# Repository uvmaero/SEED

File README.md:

# SEED
23-24 Battery design BMS

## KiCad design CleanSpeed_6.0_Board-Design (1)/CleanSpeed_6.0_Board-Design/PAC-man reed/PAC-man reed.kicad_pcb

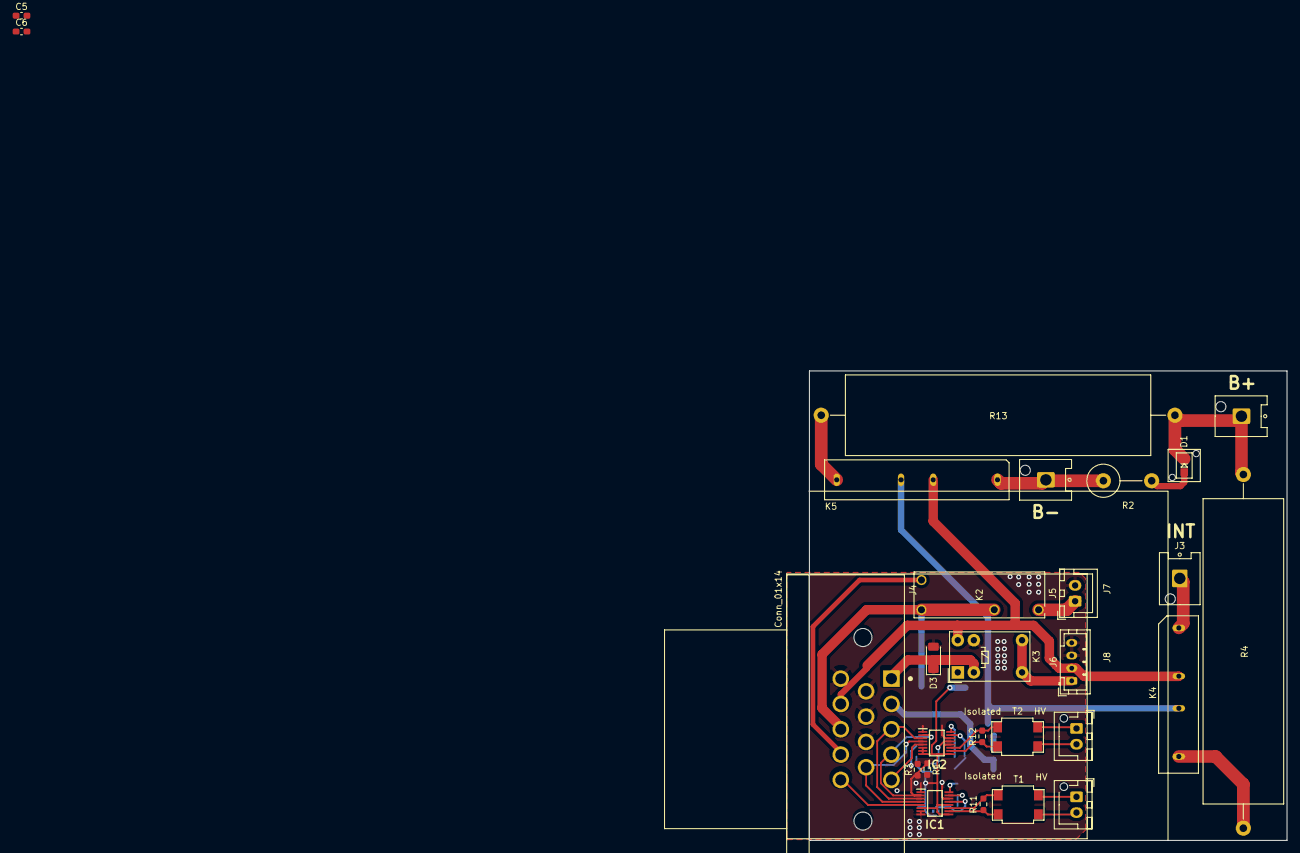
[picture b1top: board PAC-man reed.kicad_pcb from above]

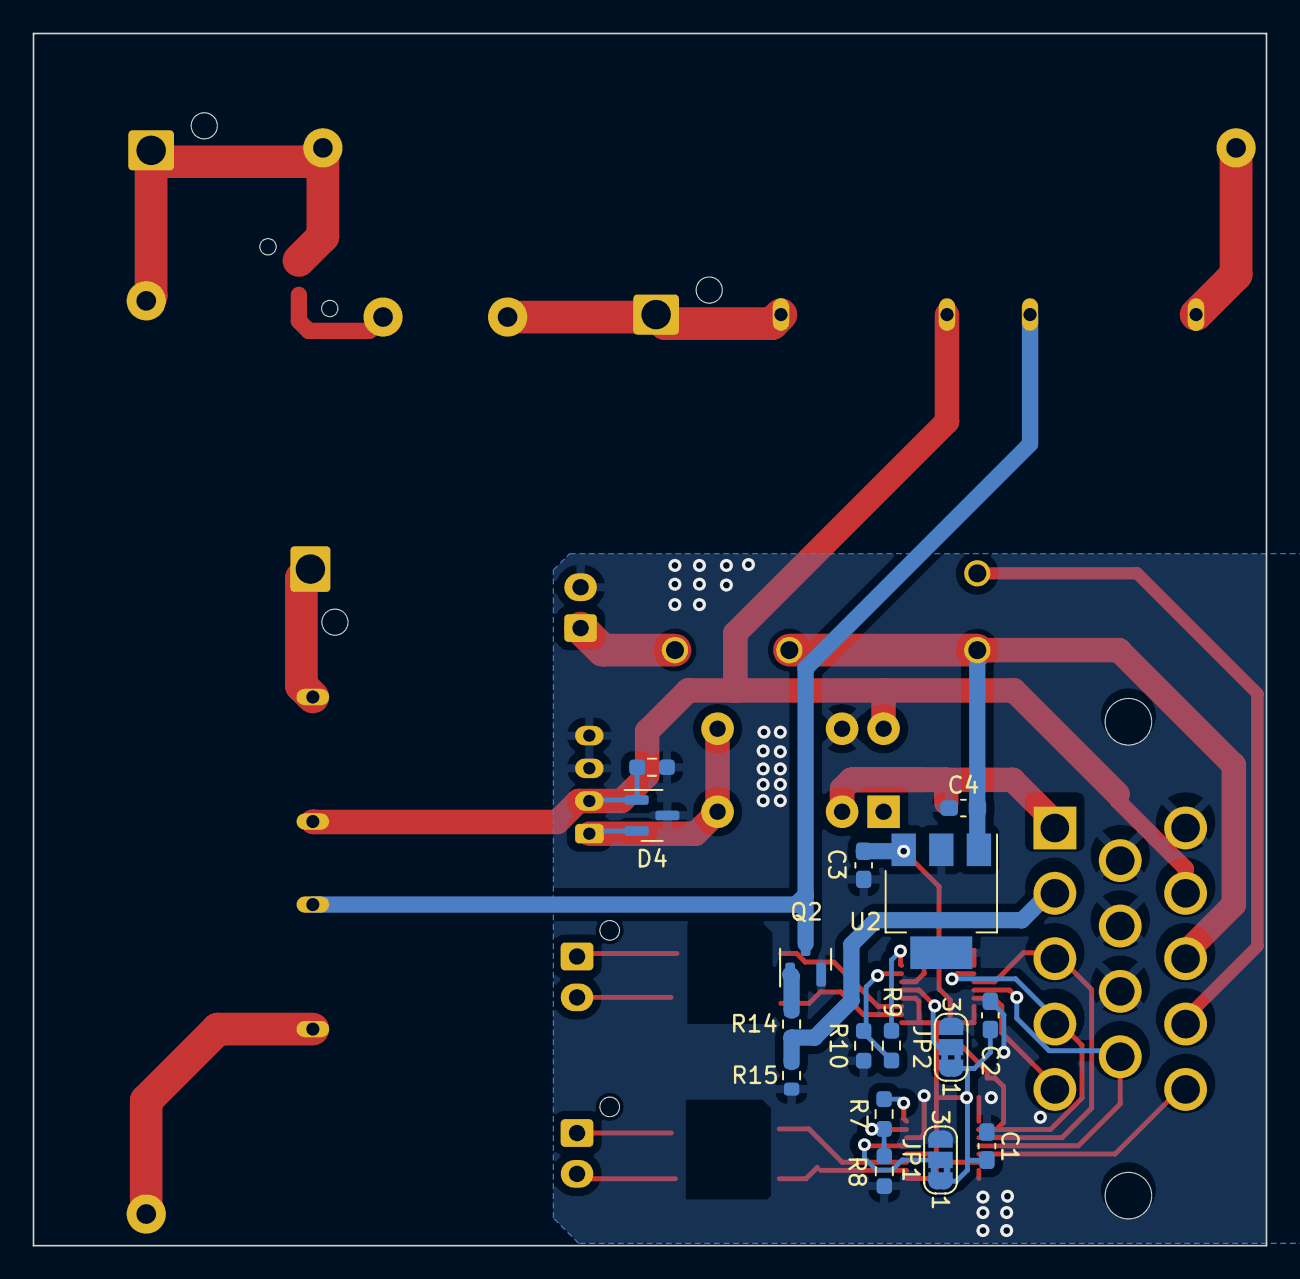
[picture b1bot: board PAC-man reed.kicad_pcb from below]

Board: 2 copper layers, 75.5 x 74.2 mm, 43 parts (16 on the bottom side), 34 nets.

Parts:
C1, C2, C5, C6: .1u; C_0603_1608Metric_Pad1.08x0.95mm_HandSolder
C3, C4: 10u; C_0603_1608Metric_Pad1.08x0.95mm_HandSolder
D1: LED; LPA-C011301S-x LED 0805 LIGHT PIPE SINGLE VERT SMD
D3: 1N4148; D_MiniMELF
D4: MMBZxx; SOT-23
IC1, IC2: LTC6820HMS#3ZZPBF; SOP50P490X110-16N
J1, J2, J3: Conn_01x01; Hirose_DF63M-1P-3.96DSA_1x01_P3.96mm_Vertical
J4: Conn_01x14; TE_1-776266-1_14pin_Horizontal
J5: Conn_01x02; JST_XH_B2B-XH-A_1x02_P2.50mm_Vertical
J6: JST PH; JST_PH_B4B-PH-K_1x04_P2.00mm_Vertical
J7, J8: Conn_01x02; JST_XH_B2B-XH-AM_1x02_P2.50mm_Vertical
JP1, JP2: Fast / Slow; SolderJumper-3_P1.3mm_Bridged2Bar12_RoundedPad1.0x1.5mm_Num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
K2: G5NB-1A4-E DC12; RELAY_G5NB-1A DC5_OMR
K3: G5V-1; Relay_SPDT_Omron_G5V-1
K4: 374-1408-5-ND; SHV12
K5: S1-12-BDM; S1-12
Q2: MMBT2222A; SOT-23
R1, R3: 2k; R_0603_1608Metric_Pad0.98x0.95mm_HandSolder
R2: 1.5k; R_Axial_DIN0516_L15.5mm_D5.0mm_P7.62mm_Vertical
R4: 2.5K; R_Axial_Power_L48.0mm_W12.5mm_P55.88mm
R5: 15k; R_0603_1608Metric_Pad0.98x0.95mm_HandSolder
R7, R8, R9, R10: 1k; R_0603_1608Metric_Pad0.98x0.95mm_HandSolder
R11, R12: 100; R_0603_1608Metric_Pad0.98x0.95mm_HandSolder
R13: 2.5k; R_Axial_Power_L48.0mm_W12.5mm_P55.88mm
R14: 10k; R_0603_1608Metric
R15: 2k; R_0603_1608Metric
T1, T2: ESMIT-4180_C; SOIC4_CBM4D19_SUM
U2: LT1963AxST-3.3; SOT-223-3_TabPin2

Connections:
+3.3V: C1.1, C2.1, C3.1, C5.1, C6.1, IC1.6 (VDDS), IC1.9 (VDD), IC1.12 (MSTR), IC2.6 (VDDS), IC2.9 (VDD), IC2.12 (MSTR), JP1.1 (A), JP2.1 (A), R1.2, R3.2, U2.3 (OUT)
+12V: C4.1, J4.12, K2.1, K2.2, U2.1 (IN)
/AIR_B+: D4.2 (K), J6.1, K3.5, K3.6
/AIR_B-: D4.1 (K), J4.11, J6.2, K3.10, K4.2, K5.2, R5.2
/B+: J2.1, K5.1, R2.1
/B-: D1.1 (K), J1.1, R4.1, R13.1
/CS1: IC1.5 (~CS), J4.14
/CS2: IC2.5 (~CS), J4.5
/FAN: J4.13, K2.4
/FAN_OUT: J5.1, K2.3
/INT: J3.1, K4.1
/IsoSpi/IMA1: J7.2, T1.3
/IsoSpi/IMA2: J8.2, T2.3
/IsoSpi/IPA1: J7.1, T1.4
/IsoSpi/IPA2: J8.1, T2.4
/MAIN_CONT: D3.1 (K), J4.1, K3.2
/MISO: IC1.3 (MISO), IC2.3 (MISO), J4.3
/MOSI: IC1.2 (MOSI), IC2.2 (MOSI), J4.4, R1.1, R3.1
/PRECHARGE: J4.2, R14.2, R15.2
/Relay_Drive: K4.3, K5.3, Q2.3 (C)
/SCK: IC1.4 (SCK), IC2.4 (SCK), J4.9
GND: C1.2, C2.2, C3.2, C4.2, C5.2, C6.2, D3.2 (A), D4.3 (A), IC1.1 (EN), IC1.7 (POL), IC1.8 (PHA), IC1.13 (SLOW), IC1.14 (GND), IC2.1 (EN), IC2.7 (POL), IC2.8 (PHA), IC2.13 (SLOW), IC2.14 (GND), J4.6, J4.7, J4.8, J4.10, J5.2, J6.3, J6.4, JP1.3 (B), JP2.3 (B), K3.9, Q2.2 (E), R5.1, R8.2, R10.2, R15.1, U2.2 (GND)
unnamed: D1.2 (A), R2.2
unnamed: IC1.16 (IBIAS), R7.1
unnamed: IC1.15 (ICMP), R7.2, R8.1
unnamed: IC1.10 (IM), R11.2, T1.2
unnamed: IC1.11 (IP), R11.1, T1.1
unnamed: IC2.16 (IBIAS), R9.1
unnamed: IC2.15 (ICMP), R9.2, R10.1
unnamed: IC2.10 (IM), R12.2, T2.2
unnamed: IC2.11 (IP), R12.1, T2.1
unnamed: K4.4, R4.2
unnamed: K5.4, R13.2
unnamed: Q2.1 (B), R14.1

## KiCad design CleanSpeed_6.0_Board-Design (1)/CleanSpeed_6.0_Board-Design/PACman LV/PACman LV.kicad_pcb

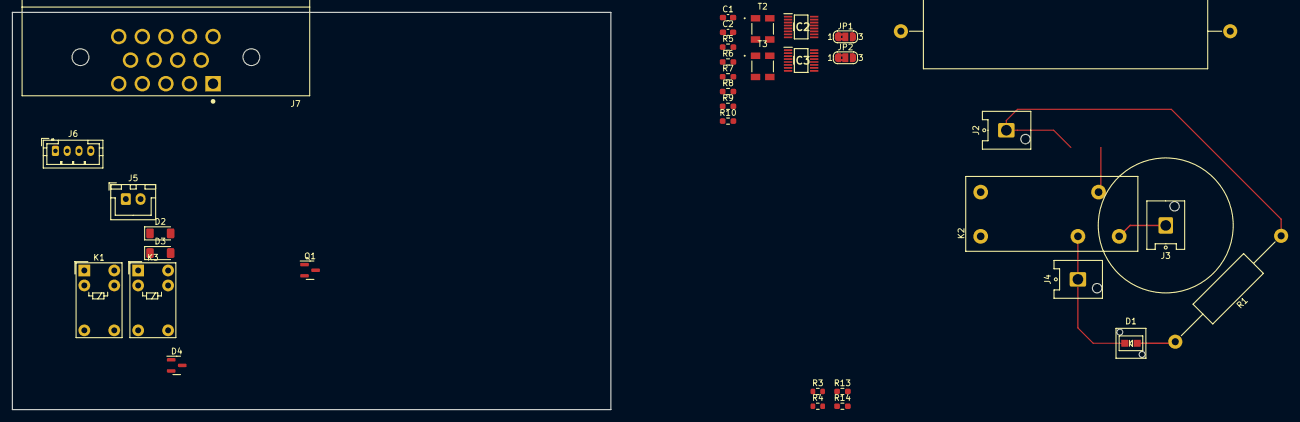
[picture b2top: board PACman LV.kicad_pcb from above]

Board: 2 copper layers, 101.6 x 67.4 mm, 34 parts (0 on the bottom side), 31 nets.

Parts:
C1, C2: 0.01u; C_0603_1608Metric_Pad1.08x0.95mm_HandSolder
D1: LED; LPA-C011301S-x LED 0805 LIGHT PIPE SINGLE VERT SMD
D2, D3: 1N4148; D_MiniMELF
D4: MMBZxx; SOT-23
IC2, IC3: LTC6820HMS#3ZZPBF; SOP50P490X110-16N
J2, J3, J4: Conn_01x01; Hirose_DF63M-1P-3.96DSA_1x01_P3.96mm_Vertical
J5: Conn_01x02; JST_XH_B2B-XH-A_1x02_P2.50mm_Vertical
J6: JST PH; JST_PH_B4B-PH-K_1x04_P2.00mm_Vertical
J7: Conn_01x14; TE_1-776266-1_14pin_Horizontal
JP1, JP2: Fast / Slow; SolderJumper-3_P1.3mm_Bridged2Bar12_RoundedPad1.0x1.5mm_Num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
K1, K3: G5V-1; Relay_SPDT_Omron_G5V-1
K2: G2RL
Q1: MMBT2222A; SOT-23
R1: 1.5k; R_Axial_DIN0414_L11.9mm_D4.5mm_P25.40mm_Horizontal
R2: 5k; R_Axial_Power_L48.0mm_W12.5mm_P55.88mm
R3: 10k; R_0603_1608Metric
R4: 2k; R_0603_1608Metric
R5, R10: 60; R_0603_1608Metric_Pad0.98x0.95mm_HandSolder
R6, R7, R8, R9: 1k; R_0603_1608Metric_Pad0.98x0.95mm_HandSolder
R13, R14: 5k; R_0603_1608Metric_Pad0.98x0.95mm_HandSolder
T2, T3: CoilCraft; SRF4532-220Y

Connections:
+3.3V: C1.1, C2.1, IC2.6 (VDDS), IC2.7 (POL), IC2.8 (PHA), IC2.9 (VDD), IC2.12 (MSTR), IC3.6 (VDDS), IC3.9 (VDD), IC3.12 (MSTR), JP1.2 (C), JP2.2 (C), R13.1, R14.1
+12V: J7.12, K1.2, K1.5, K1.6
/AIR_B+: D4.2 (K), J6.2, K3.5, K3.6
/AIR_B-: D2.1 (K), D4.1 (K), J6.1, J7.9, K2.2, K3.10
/B+: J3.1, K2.10
/CS1: IC3.5 (~CS), J7.6, R13.2
/CS2: IC2.5 (~CS), J7.5, R14.2
/FAN: J7.13, K1.9
/FAN_OUT: J5.1, K1.10
/INT+: J2.1, R1.1, R2.1
/INT-: D1.1 (K), J4.1, K2.1
/MAIN_CONT: D3.1 (K), J7.8, K3.2
/MISO: IC2.3 (MISO), IC3.3 (MISO), J7.10
/MOSI: IC2.2 (MOSI), IC3.2 (MOSI), J7.7
/PRECHARGE: J7.11, R3.2, R4.2
/SCK: IC2.4 (SCK), IC3.4 (SCK), J7.4
GND: C1.2, C2.2, D3.2 (A), D4.3 (A), IC2.1 (EN), IC2.14 (GND), IC3.1 (EN), IC3.7 (POL), IC3.8 (PHA), IC3.14 (GND), J5.2, J6.3, J6.4, J7.14, JP1.3 (B), JP2.3 (B), K3.9, Q1.2 (E), R4.1, R7.2, R9.2
unnamed: D1.2 (A), R1.2
unnamed: D2.2 (A), K2.9, Q1.3 (C)
unnamed: IC2.16 (IBIAS), R6.1
unnamed: IC2.15 (ICMP), R6.2, R7.1
unnamed: IC2.10 (IM), R5.2, T2.2 (AB)
unnamed: IC2.11 (IP), R5.1, T2.1 (AA)
unnamed: IC2.13 (SLOW), JP1.1 (A)
unnamed: IC3.16 (IBIAS), R8.1
unnamed: IC3.15 (ICMP), R8.2, R9.1
unnamed: IC3.10 (IM), R10.2, T3.2 (AB)
unnamed: IC3.11 (IP), R10.1, T3.1 (AA)
unnamed: IC3.13 (SLOW), JP2.1 (A)
unnamed: K2.5, R2.2
unnamed: Q1.1 (B), R3.1

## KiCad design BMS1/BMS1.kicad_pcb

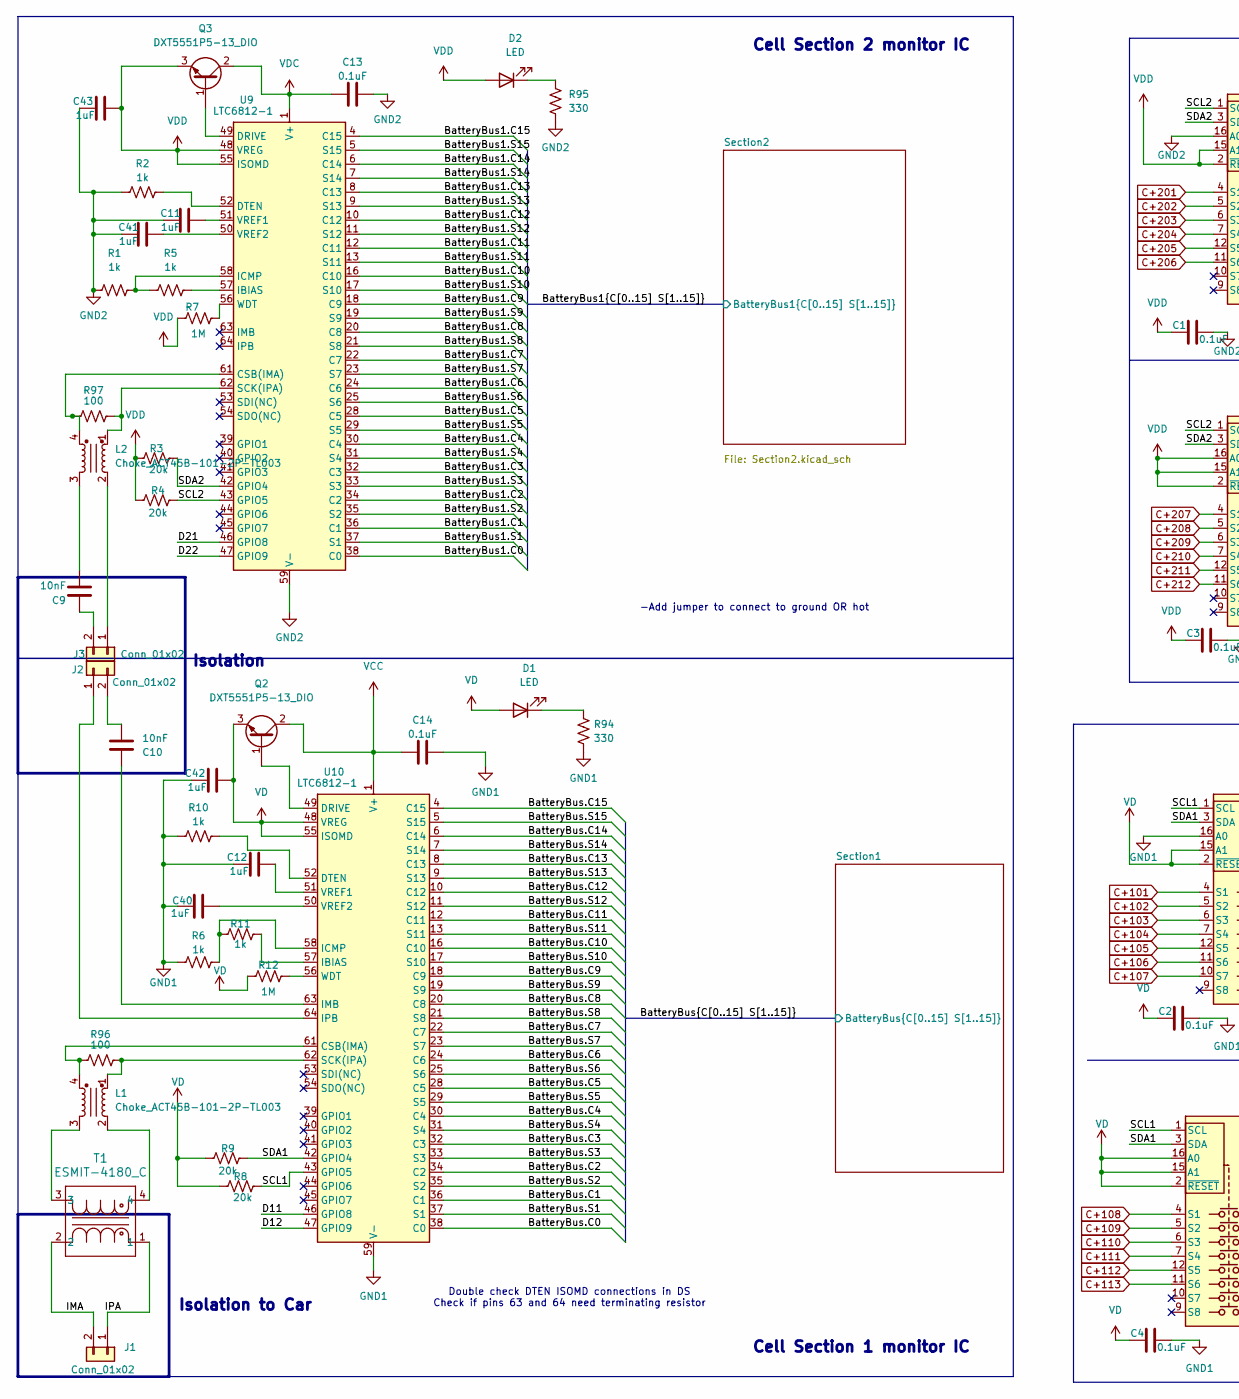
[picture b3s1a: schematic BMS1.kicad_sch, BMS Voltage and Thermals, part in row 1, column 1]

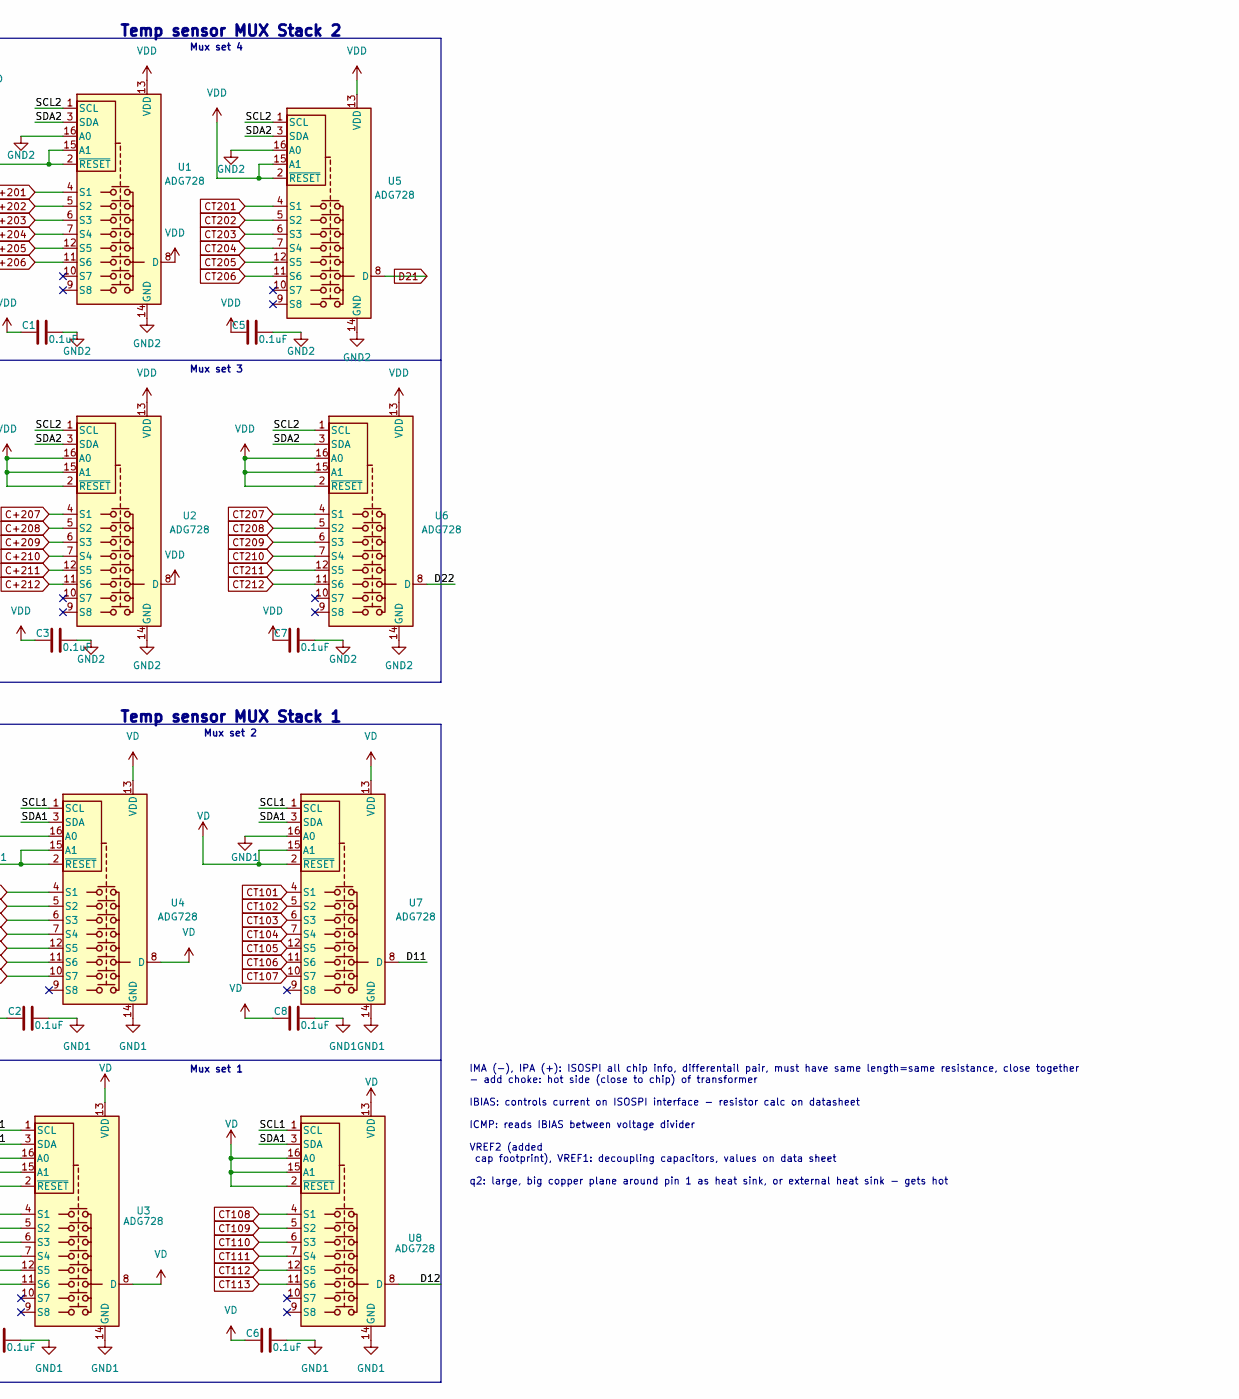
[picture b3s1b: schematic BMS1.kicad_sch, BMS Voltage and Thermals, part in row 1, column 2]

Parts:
C1, C2, C3, C4, C5, C6, C7, C8, C13, C14: 0.1uF; C_0603_1608Metric; MPN AGC0603X7R101-104KXP
C9, C10: 10nF; C_0805_2012Metric; MPN C0805C103K5RACTU
C11, C12, C40, C41, C42, C43: 1uF; C_0603_1608Metric; MPN CL10B105KP8NNNC
D1, D2: LED; LED_0201_0603Metric; MPN LED WHITE DIFFUSED 2SMD
J1: Conn_01x02; JST_XH_S2B-XH-A-1_1x02_P2.50mm_Horizontal; MPN S2B-XH-A-1
J2, J3: Conn_01x02; JST_XH_B2B-XH-A_1x02_P2.50mm_Vertical; MPN B2B-XH-A
L1, L2: Choke_ACT45B-101-2P-TL003; ACT45B-101-2P-TL003_TDK_new; MPN ACT45B-101-2P-TL003
Q2, Q3: DXT5551P5-13_DIO; DXT5551P5-13_DIO-M; MPN DXT5551P5-13
R1, R2, R5, R6, R10, R11: 1k; R_0603_1608Metric; MPN RC0603FR-071KL
R3, R4, R8, R9: 20k; R_0603_1608Metric; MPN ERJ-3EKF2002V
R7, R12: 1M; R_0603_1608Metric; MPN ERJ-3EKF1004V
R94, R95: 330; R_0603_1608Metric; MPN ERA-3AEB331V
R96, R97: 100; R_0805_2012Metric; MPN CSP0603AN101-WP30300563001-3T
T1: ESMIT-4180_C; SOIC4_CBM4D19_SUM; MPN ESMIT-4180/C
U1, U2, U3, U4, U5, U6, U7, U8: ADG728; TSSOP-16_4.4x5mm_P0.65mm; MPN ADG728BRUZ-REEL7
U9, U10: LTC6812-1; QFP-64_11x11_Pitch0.5mm; MPN LTC6812ILWE-1#3ZZTRPBF

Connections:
/BatteryBus1.C0: U9.38 (C0); also elsewhere on the board
/BatteryBus1.C1: U9.36 (C1); also elsewhere on the board
/BatteryBus1.C2: U9.34 (C2); also elsewhere on the board
/BatteryBus1.C3: U9.32 (C3); also elsewhere on the board
/BatteryBus1.C4: U9.30 (C4); also elsewhere on the board
/BatteryBus1.C5: U9.28 (C5); also elsewhere on the board
/BatteryBus1.C6: U9.24 (C6); also elsewhere on the board
/BatteryBus1.C7: U9.22 (C7); also elsewhere on the board
/BatteryBus1.C8: U9.20 (C8); also elsewhere on the board
/BatteryBus1.C9: U9.18 (C9); also elsewhere on the board
/BatteryBus1.C10: U9.16 (C10); also elsewhere on the board
/BatteryBus1.C11: U9.12 (C11); also elsewhere on the board
/BatteryBus1.C12: U9.10 (C12); also elsewhere on the board
/BatteryBus1.C13: U9.4 (C15), U9.6 (C14), U9.8 (C13); also elsewhere on the board
/BatteryBus1.S1: U9.37 (S1); also elsewhere on the board
/BatteryBus1.S2: U9.35 (S2); also elsewhere on the board
/BatteryBus1.S3: U9.33 (S3); also elsewhere on the board
/BatteryBus1.S4: U9.31 (S4); also elsewhere on the board
/BatteryBus1.S5: U9.29 (S5); also elsewhere on the board
/BatteryBus1.S6: U9.25 (S6); also elsewhere on the board
/BatteryBus1.S7: U9.23 (S7); also elsewhere on the board
/BatteryBus1.S8: U9.21 (S8); also elsewhere on the board
/BatteryBus1.S9: U9.19 (S9); also elsewhere on the board
/BatteryBus1.S10: U9.17 (S10); also elsewhere on the board
/BatteryBus1.S11: U9.13 (S11); also elsewhere on the board
/BatteryBus1.S12: U9.11 (S12); also elsewhere on the board
/BatteryBus1.S13: U9.9 (S13)
/BatteryBus1.S14: U9.7 (S14)
/BatteryBus1.S15: U9.5 (S15)
/BatteryBus.C0: U10.38 (C0); also elsewhere on the board
/BatteryBus.C1: U10.36 (C1); also elsewhere on the board
/BatteryBus.C2: U10.34 (C2); also elsewhere on the board
/BatteryBus.C3: U10.32 (C3); also elsewhere on the board
/BatteryBus.C4: U10.30 (C4); also elsewhere on the board
/BatteryBus.C5: U10.28 (C5); also elsewhere on the board
/BatteryBus.C6: U10.24 (C6); also elsewhere on the board
/BatteryBus.C7: U10.22 (C7); also elsewhere on the board
/BatteryBus.C8: U10.20 (C8); also elsewhere on the board
/BatteryBus.C9: U10.18 (C9); also elsewhere on the board
/BatteryBus.C10: U10.16 (C10); also elsewhere on the board
/BatteryBus.C11: U10.12 (C11); also elsewhere on the board
/BatteryBus.C12: U10.10 (C12); also elsewhere on the board
/BatteryBus.C13: U10.8 (C13); also elsewhere on the board
/BatteryBus.C14: U10.4 (C15), U10.6 (C14); also elsewhere on the board
/BatteryBus.S1: U10.37 (S1); also elsewhere on the board
/BatteryBus.S2: U10.35 (S2); also elsewhere on the board
/BatteryBus.S3: U10.33 (S3); also elsewhere on the board
/BatteryBus.S4: U10.31 (S4); also elsewhere on the board
/BatteryBus.S5: U10.29 (S5); also elsewhere on the board
/BatteryBus.S6: U10.25 (S6); also elsewhere on the board
/BatteryBus.S7: U10.23 (S7); also elsewhere on the board
/BatteryBus.S8: U10.21 (S8); also elsewhere on the board
/BatteryBus.S9: U10.19 (S9); also elsewhere on the board
/BatteryBus.S10: U10.17 (S10); also elsewhere on the board
/BatteryBus.S11: U10.13 (S11); also elsewhere on the board
/BatteryBus.S12: U10.11 (S12); also elsewhere on the board
/BatteryBus.S13: U10.9 (S13); also elsewhere on the board
/BatteryBus.S14: U10.7 (S14)
/BatteryBus.S15: U10.5 (S15)
/D11: U7.8 (D), U10.46 (GPIO8)
/D12: U8.8 (D), U10.47 (GPIO9)
/D22: U6.8 (D), U9.47 (GPIO9)
/IMA: J1.2, T1.2
/IPA: J1.1, T1.1
/SCL1: R8.2, U3.1 (SCL), U4.1 (SCL), U7.1 (SCL), U8.1 (SCL), U10.43 (GPIO5)
/SCL2: R4.2, U1.1 (SCL), U2.1 (SCL), U5.1 (SCL), U6.1 (SCL), U9.43 (GPIO5)
/SDA1: R9.2, U3.3 (SDA), U4.3 (SDA), U7.3 (SDA), U8.3 (SDA), U10.42 (GPIO4)
/SDA2: R3.2, U1.3 (SDA), U2.3 (SDA), U5.3 (SDA), U6.3 (SDA), U9.42 (GPIO4)
C+101: U4.4 (S1); also elsewhere on the board
C+102: U4.5 (S2); also elsewhere on the board
C+103: U4.6 (S3); also elsewhere on the board
C+104: U4.7 (S4); also elsewhere on the board
C+105: U4.12 (S5); also elsewhere on the board
C+106: U4.11 (S6); also elsewhere on the board
C+107: U4.10 (S7); also elsewhere on the board
C+108: U3.4 (S1); also elsewhere on the board
C+109: U3.5 (S2); also elsewhere on the board
C+110: U3.6 (S3); also elsewhere on the board
C+111: U3.7 (S4); also elsewhere on the board
C+112: U3.12 (S5); also elsewhere on the board
C+113: U3.11 (S6); also elsewhere on the board
C+201: U1.4 (S1); also elsewhere on the board
C+202: U1.5 (S2); also elsewhere on the board
C+203: U1.6 (S3); also elsewhere on the board
C+204: U1.7 (S4); also elsewhere on the board
C+205: U1.12 (S5); also elsewhere on the board
C+206: U1.11 (S6); also elsewhere on the board
C+207: U2.4 (S1); also elsewhere on the board
C+208: U2.5 (S2); also elsewhere on the board
C+209: U2.6 (S3); also elsewhere on the board
C+210: U2.7 (S4); also elsewhere on the board
C+211: U2.12 (S5); also elsewhere on the board
C+212: U2.11 (S6); also elsewhere on the board
CT101: U7.4 (S1); also elsewhere on the board
CT102: U7.5 (S2); also elsewhere on the board
CT103: U7.6 (S3); also elsewhere on the board
CT104: U7.7 (S4); also elsewhere on the board
CT105: U7.12 (S5); also elsewhere on the board
CT106: U7.11 (S6); also elsewhere on the board
CT107: U7.10 (S7); also elsewhere on the board
CT108: U8.4 (S1); also elsewhere on the board
CT109: U8.5 (S2); also elsewhere on the board
CT110: U8.6 (S3); also elsewhere on the board
CT111: U8.7 (S4); also elsewhere on the board
CT112: U8.12 (S5); also elsewhere on the board
CT113: U8.11 (S6); also elsewhere on the board
CT201: U5.4 (S1); also elsewhere on the board
CT202: U5.5 (S2); also elsewhere on the board
CT203: U5.6 (S3); also elsewhere on the board
CT204: U5.7 (S4); also elsewhere on the board
CT205: U5.12 (S5); also elsewhere on the board
CT206: U5.11 (S6); also elsewhere on the board
CT207: U6.4 (S1); also elsewhere on the board
CT208: U6.5 (S2); also elsewhere on the board
CT209: U6.6 (S3); also elsewhere on the board
CT210: U6.7 (S4); also elsewhere on the board
CT211: U6.12 (S5); also elsewhere on the board
CT212: U6.11 (S6); also elsewhere on the board
D21: U5.8 (D), U9.46 (GPIO8)
GND1: C2.1, C4.1, C6.1, C8.1, C12.1, C14.2, C40.1, C42.1, R6.1, R10.1, R94.1, U3.14 (GND), U4.14 (GND), U4.16 (A0), U7.14 (GND), U7.16 (A0), U8.14 (GND), U10.59 (V-), U10.60 (V-), U10.65 (V-); also elsewhere on the board
GND2: C1.1, C3.1, C5.1, C7.1, C11.1, C13.2, C41.1, C43.1, R1.1, R2.1, R95.1, U1.14 (GND), U1.16 (A0), U2.14 (GND), U5.14 (GND), U5.16 (A0), U6.14 (GND), U9.59 (V-), U9.60 (V-), U9.65 (V-); also elsewhere on the board
unnamed: C9.1, L2.3
unnamed: D1.1 (K), R94.2
unnamed: D2.1 (K), R95.2
unnamed: J2.1, U10.64 (IPB)
unnamed: C10.1, J2.2
unnamed: J3.1, L2.2
unnamed: C9.2, J3.2
unnamed: L1.2, T1.4
unnamed: L1.3, T1.3
unnamed: Q2.1 (B), U10.49 (DRIVE)
unnamed: Q3.1 (B), U9.49 (DRIVE)
unnamed: R2.2, U9.52 (DTEN)
unnamed: R5.2, U9.57 (IBIAS)
unnamed: R1.2, R5.1, U9.58 (ICMP)
unnamed: C11.2, U9.51 (VREF1)
unnamed: C41.2, U9.50 (VREF2)
unnamed: R7.2, U9.56 (WDT)
unnamed: L1.4, R96.1, U10.61 (CSB(IMA))
unnamed: R10.2, U10.52 (DTEN)
unnamed: R11.2, U10.57 (IBIAS)
unnamed: R6.2, R11.1, U10.58 (ICMP)
unnamed: C10.2, U10.63 (IMB)
unnamed: L1.1, R96.2, U10.62 (SCK(IPA))
unnamed: C12.2, U10.51 (VREF1)
unnamed: C40.2, U10.50 (VREF2)
unnamed: R12.2, U10.56 (WDT)
VCC: C14.1, Q2.2 (C), U10.1 (V+); also elsewhere on the board
VD: C2.2, C4.2, C6.2, C8.2, C42.2, D1.2 (A), Q2.3 (E), R8.1, R9.1, R12.1, U3.2 (~RESET), U3.8 (D), U3.13 (VDD), U3.15 (A1), U3.16 (A0), U4.2 (~RESET), U4.8 (D), U4.13 (VDD), U4.15 (A1), U7.2 (~RESET), U7.13 (VDD), U7.15 (A1), U8.2 (~RESET), U8.13 (VDD), U8.15 (A1), U8.16 (A0), U10.48 (VREG), U10.55 (ISOMD)
VDC: C13.1, Q3.2 (C), U9.1 (V+); also elsewhere on the board
VDD: C1.2, C3.2, C5.2, C7.2, C43.2, D2.2 (A), Q3.3 (E), R3.1, R4.1, R7.1, U1.2 (~RESET), U1.8 (D), U1.13 (VDD), U1.15 (A1), U2.2 (~RESET), U2.8 (D), U2.13 (VDD), U2.15 (A1), U2.16 (A0), U5.2 (~RESET), U5.13 (VDD), U5.15 (A1), U6.2 (~RESET), U6.13 (VDD), U6.15 (A1), U6.16 (A0), U9.48 (VREG), U9.55 (ISOMD)

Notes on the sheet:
Mux set 4
-Add jumper to connect to ground OR hot
IMA (-), IPA (+): ISOSPI all chip info, differentail pair, must have same length=same resistance, close together - add choke: hot side (close to chip) of transformer IBIAS: controls current on ISOSPI interface - resistor calc on datasheet ICMP: reads IBIAS between voltage divider VREF2 (added cap f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
Cell Section 1 monitor IC
Temp sensor MUX Stack 2
Cell Section 2 monitor IC
Temp sensor MUX Stack 1
Isolation to Car
Mux set 1
Mux set 2
Double check DTEN ISOMD connections in DS Check if pins 63 and 64 need terminating resistor
Isolation
Mux set 3

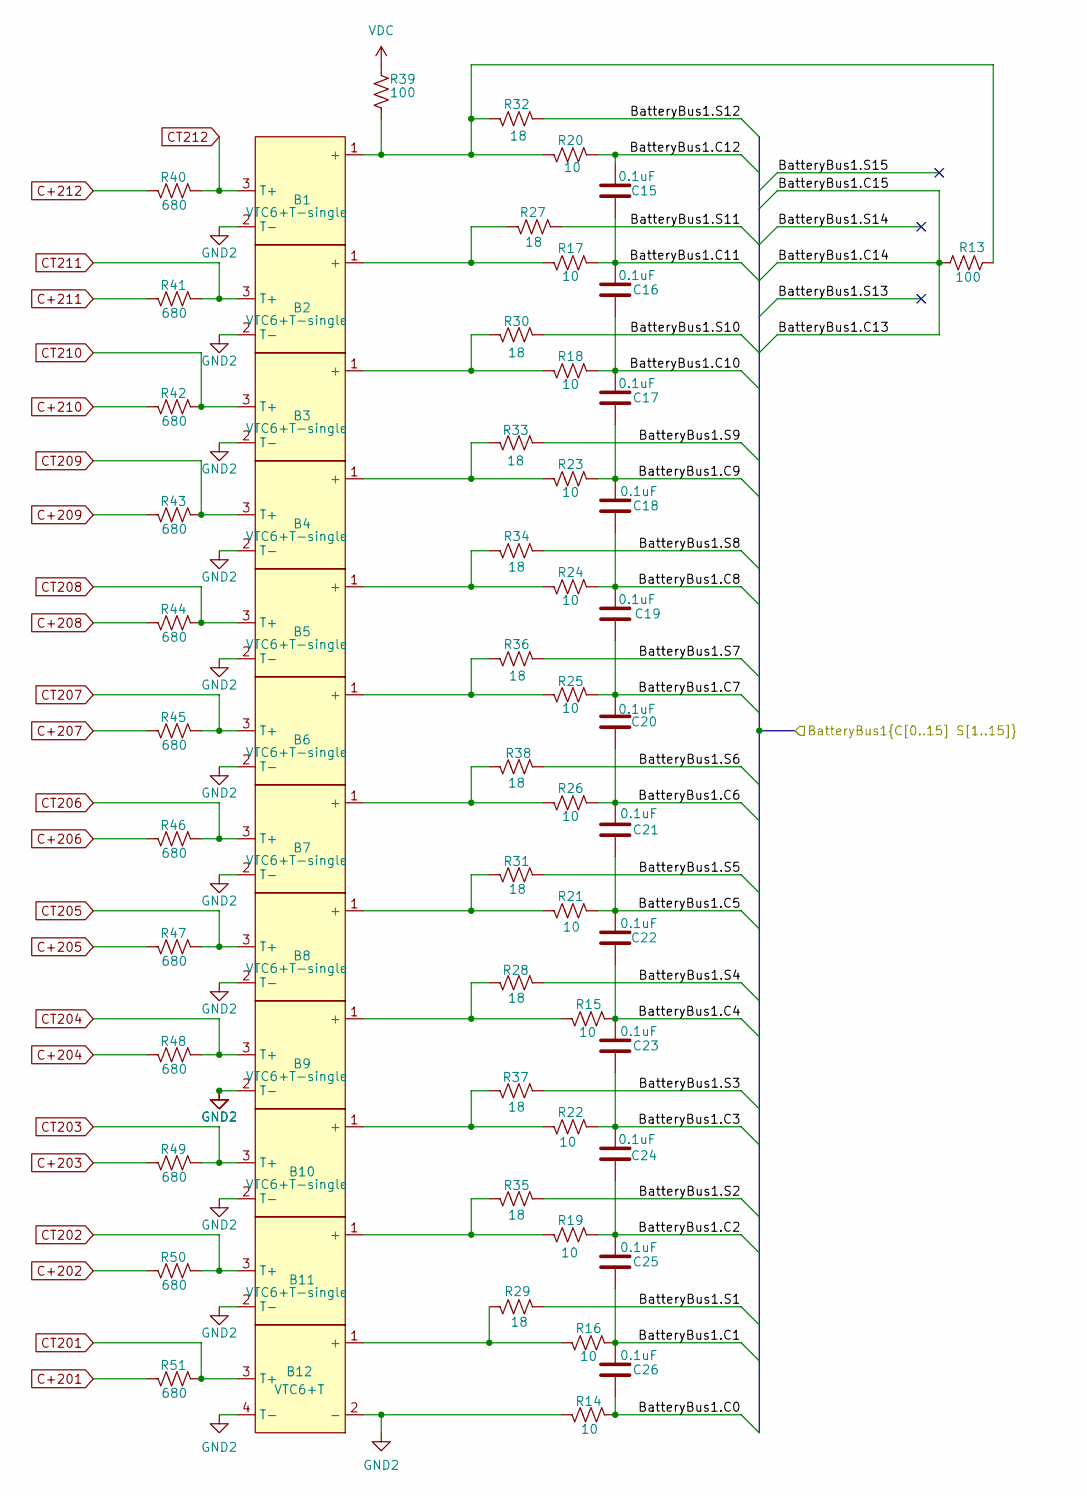
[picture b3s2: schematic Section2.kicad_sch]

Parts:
B1, B2, B3, B4, B5, B6, B7, B8, B9, B10, B11: VTC6+T-single; VTC-6-single
B12: VTC6+T; VTC-6
C15, C16, C17, C18, C19, C20, C21, C22, C23, C24, C25, C26: 0.1uF; C_0603_1608Metric; MPN AGC0603X7R101-104KXP
R13: 100; R_0805_2012Metric; MPN RMCF0805FT100R
R14, R15, R16, R17, R18, R19, R20, R21, R22, R23, R24, R25, R26: 10; R_0805_2012Metric; MPN ERJ-P06J100V
R27, R28, R29, R30, R31, R32, R33, R34, R35, R36, R37, R38: 18; R_2512_6332Metric; MPN RMCF2512FT18R0
R39: 100; R_0603_1608Metric; MPN ERJ-3EKF1000V
R40, R41, R42, R43, R44, R45, R46, R47, R48, R49, R50, R51: 680; R_0603_1608Metric; MPN RC0603JR-07680RL

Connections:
/BatteryBus1.C0: C26.2, R14.2; also elsewhere on the board
/BatteryBus1.C1: C25.2, C26.1, R16.2; also elsewhere on the board
/BatteryBus1.C2: C24.2, C25.1, R19.2; also elsewhere on the board
/BatteryBus1.C3: C23.2, C24.1, R22.2; also elsewhere on the board
/BatteryBus1.C4: C22.2, C23.1, R15.2; also elsewhere on the board
/BatteryBus1.C5: C21.2, C22.1, R21.2; also elsewhere on the board
/BatteryBus1.C6: C20.2, C21.1, R26.2; also elsewhere on the board
/BatteryBus1.C7: C19.2, C20.1, R25.2; also elsewhere on the board
/BatteryBus1.C8: C18.2, C19.1, R24.2; also elsewhere on the board
/BatteryBus1.C9: C17.2, C18.1, R23.2; also elsewhere on the board
/BatteryBus1.C10: C16.2, C17.1, R18.2; also elsewhere on the board
/BatteryBus1.C11: C15.2, C16.1, R17.2; also elsewhere on the board
/BatteryBus1.C12: C15.1, R20.2; also elsewhere on the board
/BatteryBus1.C13: R13.1; also elsewhere on the board
/BatteryBus1.S1: R29.2; also elsewhere on the board
/BatteryBus1.S2: R35.2; also elsewhere on the board
/BatteryBus1.S3: R37.2; also elsewhere on the board
/BatteryBus1.S4: R28.2; also elsewhere on the board
/BatteryBus1.S5: R31.2; also elsewhere on the board
/BatteryBus1.S6: R38.2; also elsewhere on the board
/BatteryBus1.S7: R36.2; also elsewhere on the board
/BatteryBus1.S8: R34.2; also elsewhere on the board
/BatteryBus1.S9: R33.2; also elsewhere on the board
/BatteryBus1.S10: R30.2; also elsewhere on the board
/BatteryBus1.S11: R27.2; also elsewhere on the board
/BatteryBus1.S12: R32.2; also elsewhere on the board
C+201: R51.2; also elsewhere on the board
C+202: R50.2; also elsewhere on the board
C+203: R49.2; also elsewhere on the board
C+204: R48.2; also elsewhere on the board
C+205: R47.2; also elsewhere on the board
C+206: R46.2; also elsewhere on the board
C+207: R45.2; also elsewhere on the board
C+208: R44.2; also elsewhere on the board
C+209: R43.2; also elsewhere on the board
C+210: R42.2; also elsewhere on the board
C+211: R41.2; also elsewhere on the board
C+212: R40.2; also elsewhere on the board
CT201: B12.3 (T+), R51.1; also elsewhere on the board
CT202: B11.3 (T+), R50.1; also elsewhere on the board
CT203: B10.3 (T+), R49.1; also elsewhere on the board
CT204: B9.3 (T+), R48.1; also elsewhere on the board
CT205: B8.3 (T+), R47.1; also elsewhere on the board
CT206: B7.3 (T+), R46.1; also elsewhere on the board
CT207: B6.3 (T+), R45.1; also elsewhere on the board
CT208: B5.3 (T+), R44.1; also elsewhere on the board
CT209: B4.3 (T+), R43.1; also elsewhere on the board
CT210: B3.3 (T+), R42.1; also elsewhere on the board
CT211: B2.3 (T+), R41.1; also elsewhere on the board
CT212: B1.3 (T+), R40.1; also elsewhere on the board
GND2: B1.2 (T-), B2.2 (T-), B3.2 (T-), B4.2 (T-), B5.2 (T-), B6.2 (T-), B7.2 (T-), B8.2 (T-), B9.2 (T-), B10.2 (T-), B11.2 (T-), B12.2 (-), B12.4 (T-), R14.1; also elsewhere on the board
unnamed: B1.1 (+), R13.2, R20.1, R32.1, R39.2
unnamed: B2.1 (+), R17.1, R27.1
unnamed: B3.1 (+), R18.1, R30.1
unnamed: B4.1 (+), R23.1, R33.1
unnamed: B5.1 (+), R24.1, R34.1
unnamed: B6.1 (+), R25.1, R36.1
unnamed: B7.1 (+), R26.1, R38.1
unnamed: B8.1 (+), R21.1, R31.1
unnamed: B9.1 (+), R15.1, R28.1
unnamed: B10.1 (+), R22.1, R37.1
unnamed: B11.1 (+), R19.1, R35.1
unnamed: B12.1 (+), R16.1, R29.1
VDC: R39.1; also elsewhere on the board

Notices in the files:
parts and their libraries:
Copyright 2016 Accelerated Designs. All rights reserved.
